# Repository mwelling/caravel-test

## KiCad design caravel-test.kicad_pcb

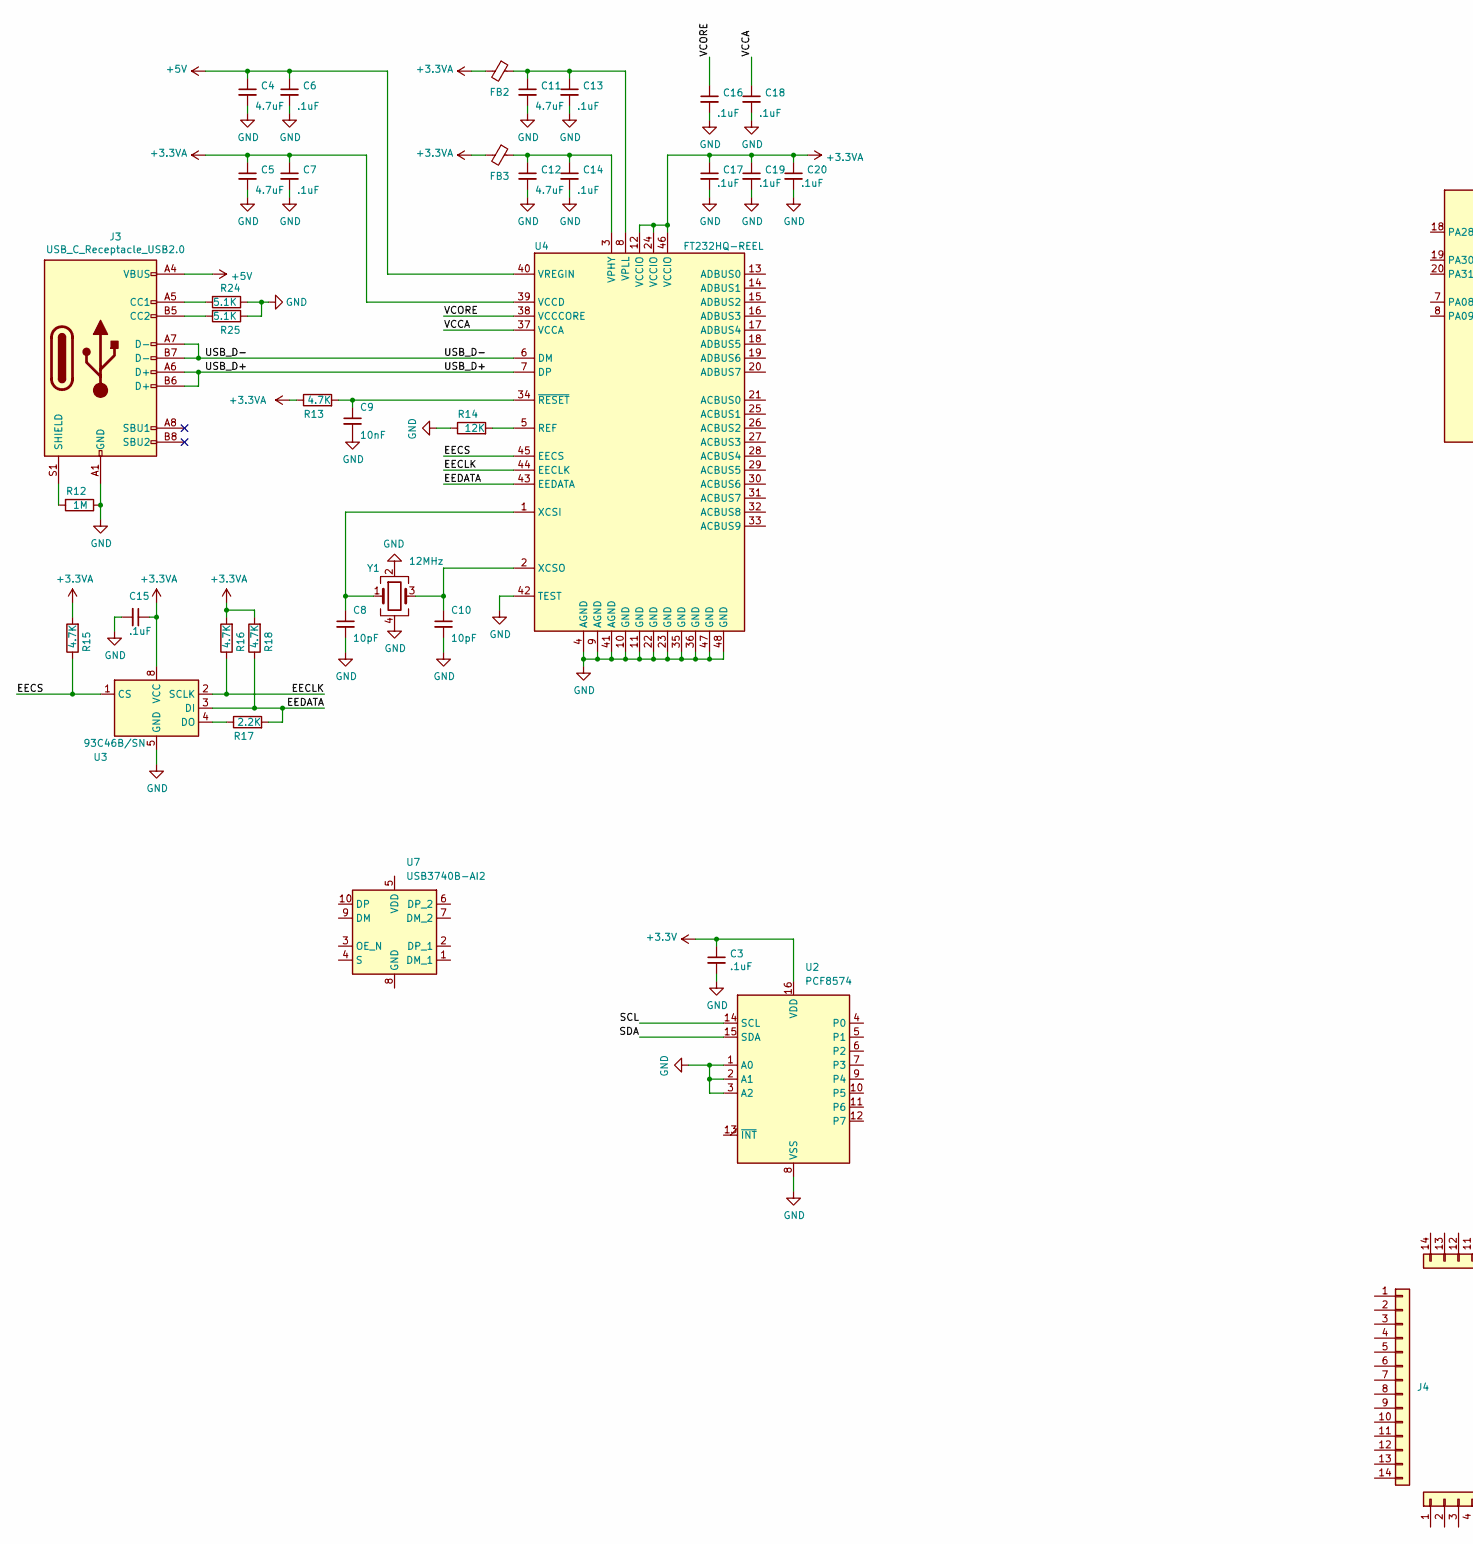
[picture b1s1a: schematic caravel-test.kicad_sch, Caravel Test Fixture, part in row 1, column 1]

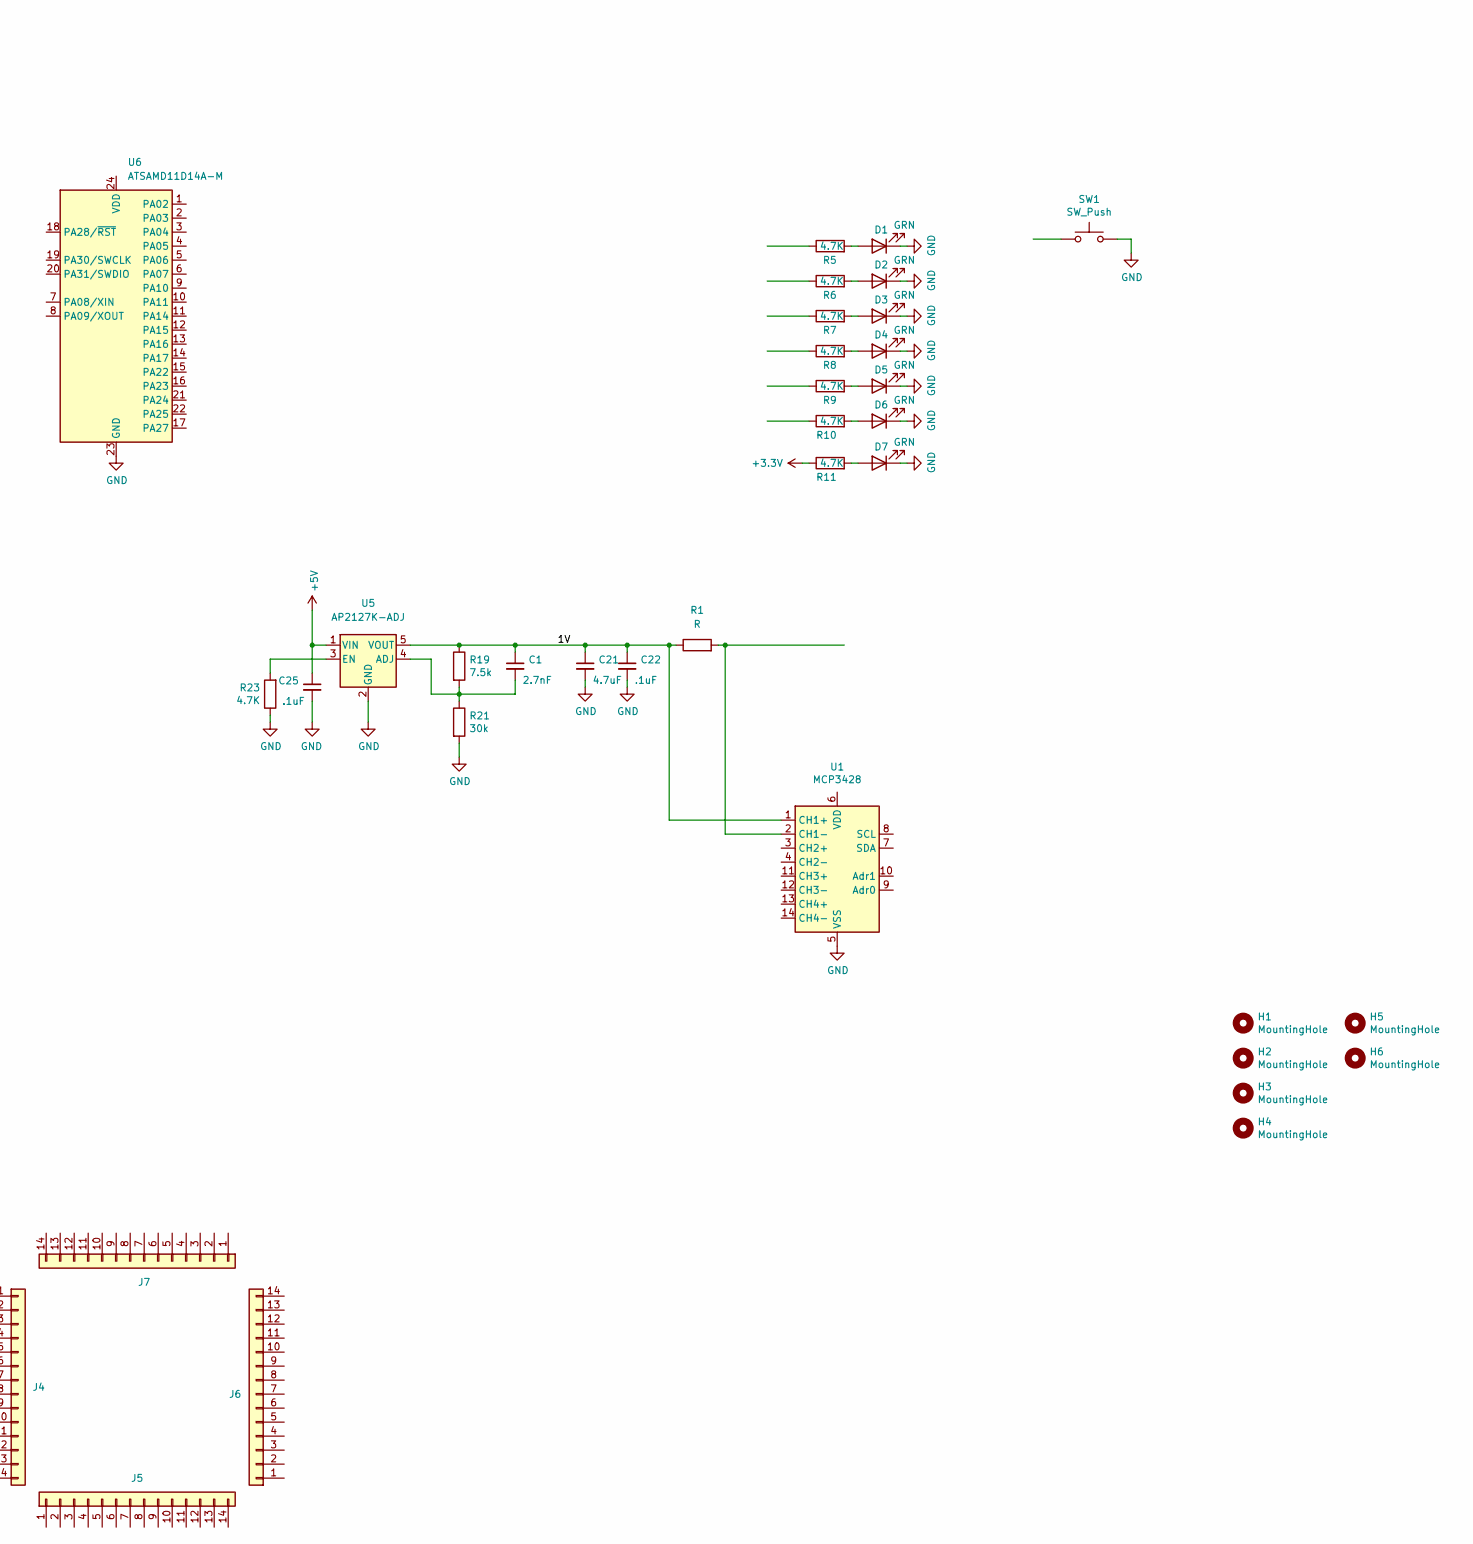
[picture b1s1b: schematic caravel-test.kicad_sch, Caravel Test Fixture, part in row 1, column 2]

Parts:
C1: 2.7nF; C_0402_1005Metric; MPN GRM155R60J475ME47D
C3, C6, C7, C13, C14, C15, C16, C17, C18, C19, C20, C22, C25: .1uF; C_0402_1005Metric; MPN GRM155R71C104KA88J
C4, C5, C21: 4.7uF; C_0402_1005Metric; MPN GRM155R60J475ME47D
C8, C10: 10pF; C_0402_1005Metric; MPN GRM1555C1H100JA01D
C9: 10nF; C_0402_1005Metric; MPN C0402C103K4RECAUTO
C11, C12: 4.7uF; C_0603_1608Metric; MPN C0603C475K9PACTU
D1, D2, D3, D4, D5, D6, D7: GRN; LED_0603_1608Metric; MPN LTST-C191GKT
FB2, FB3: Ferrite_Bead_Small; L_0603_1608Metric; MPN 742792651
H1, H2, H3, H4, H5, H6: MountingHole; MountingHole_3.5mm; MPN N/A
J3: USB_C_Receptacle_USB2.0; USB_C_Receptacle_HRO_TYPE-C-31-M-12
J4, J5, J6, J7: Conn_01x14; PinHeader_1x14_P1.27mm_Vertical
R1: R; R_1210_3225Metric
R5, R6, R7, R8, R9, R10, R11, R13, R15, R16, R18, R23: 4.7K; R_0402_1005Metric; MPN RC0402JR-074K7L
R12: 1M; R_0402_1005Metric; MPN RC0402FR-071ML
R14: 12K; R_0402_1005Metric; MPN ERA-2AEB123X
R17: 2.2K; R_0402_1005Metric; MPN ERA-2AEB222X
R19: 7.5k; R_0402_1005Metric; MPN RMCF0402FT402K
R21: 30k; R_0402_1005Metric; MPN RC0402FR-07169KL
R24, R25: 5.1K; R_0402_1005Metric; MPN RC0402FR-071ML
SW1: SW_Push; SW_SPST_EVQP0; MPN EVQ-P0N02B
U1: MCP3428
U2: PCF8574; SSOP-20_4.4x6.5mm_P0.65mm
U3: 93C46B/SN; SOIC-8_3.9x4.9mm_P1.27mm; MPN 93C46B/SN
U4: FT232HQ-REEL; QFN-48-1EP_8x8mm_P0.5mm_EP6.2x6.2mm; MPN FT232HL-REEL
U5: AP2127K-ADJ; SOT-23-5
U6: ATSAMD11D14A-M; QFN-24-1EP_4x4mm_P0.5mm_EP2.6x2.6mm
U7: USB3740B-AI2
Y1: 12MHz; Crystal_SMD_2520-4Pin_2.5x2.0mm; MPN FA-20H 12.0000MD30Z-K3

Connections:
+3.3VA: C5.1, C7.1, C15.1, C17.1, C19.1, C20.1, FB2.2, FB3.2, R13.1, R15.2, R16.2, R18.2, U3.8 (VCC), U4.12 (VCCIO), U4.24 (VCCIO), U4.39 (VCCD), U4.46 (VCCIO)
+3V3: C3.1, R11.1, U2.16 (VDD)
+5V: C4.1, C6.1, C25.1, J3.A4 (VBUS), J3.A9 (VBUS), J3.B4 (VBUS), J3.B9 (VBUS), U4.40 (VREGIN), U5.1 (VIN)
/1V: C1.1, C21.1, C22.1, R1.1, R19.1, U1.1 (CH1+), U5.5 (VOUT)
/EECLK: R16.1, U3.2 (SCLK), U4.44 (EECLK)
/EECS: R15.1, U3.1 (CS), U4.45 (EECS)
/EEDATA: R17.2, R18.1, U3.3 (DI), U4.43 (EEDATA)
/SCL: U2.14 (SCL)
/SDA: U2.15 (SDA)
/USB_D+: J3.A6 (D+), J3.B6 (D+), U4.7 (DP)
/USB_D-: J3.A7 (D-), J3.B7 (D-), U4.6 (DM)
/VCCA: C18.1, U4.37 (VCCA)
/VCORE: C16.1, U4.38 (VCCCORE)
GND: C3.2, C4.2, C5.2, C6.2, C7.2, C8.2, C9.2, C10.2, C11.2, C12.2, C13.2, C14.2, C15.2, C16.2, C17.2, C18.2, C19.2, C20.2, C21.2, C22.2, C25.2, D1.1 (K), D2.1 (K), D3.1 (K), D4.1 (K), D5.1 (K), D6.1 (K), D7.1 (K), J3.A1 (GND), J3.A12 (GND), J3.B1 (GND), J3.B12 (GND), R12.1, R14.1, R21.2, R23.1, R24.1, R25.1, SW1.2, U1.5 (VSS), U2.1 (A0), U2.2 (A1), U2.3 (A2), U2.8 (VSS), U3.5 (GND), U4.4 (AGND), U4.9 (AGND), U4.10 (GND), U4.11 (GND), U4.22 (GND), U4.23 (GND), U4.35 (GND), U4.36 (GND), U4.41 (AGND), U4.42 (TEST), U4.47 (GND), U4.48 (GND), U5.2 (GND), U6.23 (GND), Y1.2, Y1.4
unnamed: C1.2, R19.2, R21.1, U5.4 (ADJ)
unnamed: C8.1, U4.1 (XCSI), Y1.1
unnamed: C9.1, R13.2, U4.34 (~RESET)
unnamed: C10.1, U4.2 (XCSO), Y1.3
unnamed: C11.1, C13.1, FB2.1, U4.8 (VPLL)
unnamed: C12.1, C14.1, FB3.1, U4.3 (VPHY)
unnamed: D1.2 (A), R5.2
unnamed: D2.2 (A), R6.2
unnamed: D3.2 (A), R7.2
unnamed: D4.2 (A), R8.2
unnamed: D5.2 (A), R9.2
unnamed: D6.2 (A), R10.2
unnamed: D7.2 (A), R11.2
unnamed: J3.A5 (CC1), R24.2
unnamed: J3.B5 (CC2), R25.2
unnamed: J3.S1 (SHIELD), R12.2
unnamed: R14.2, U4.5 (REF)
unnamed: R17.1, U3.4 (DO)
unnamed: R23.2, U5.3 (EN)
unnamed: R1.2, U1.2 (CH1-)

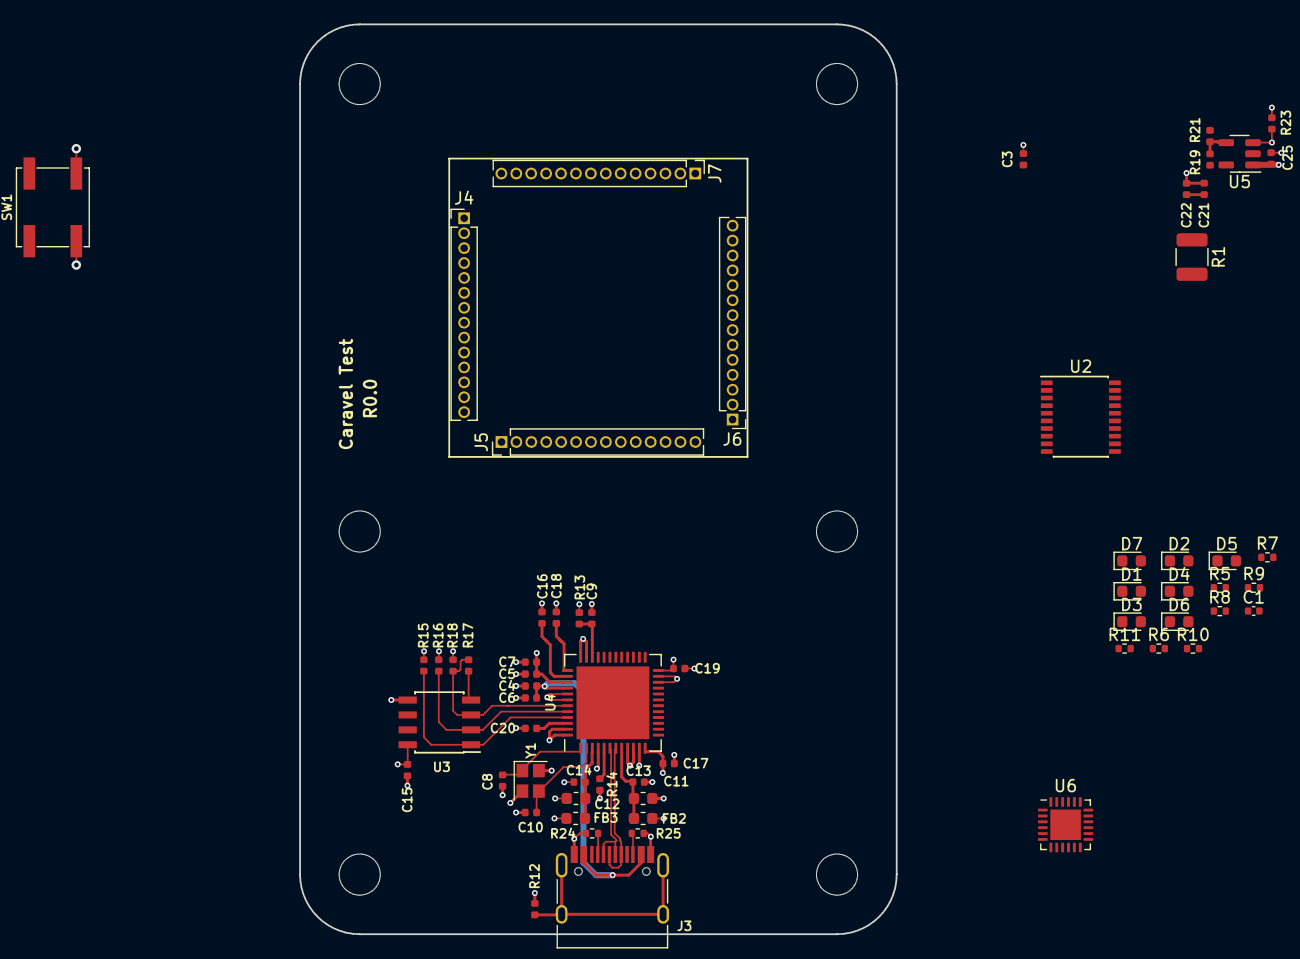
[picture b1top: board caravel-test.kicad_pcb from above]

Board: 4 copper layers, 50.8 x 77.5 mm, 69 parts (0 on the bottom side), 31 nets.

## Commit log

2021-12-22 Initial commit of caravel-test
2021-12-22 Remove automatic backups

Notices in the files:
caravel-test.kicad_sch:
(c) 2021 Michael Welling
